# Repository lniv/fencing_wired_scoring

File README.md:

# A simple fencing scoring system

The aim is to make it simple, rather than efficient or super precise.\
Towards that, the hardware is a LED display with a matching controller from adafruit,
and circuitpython is used vs e.g. C. I tried to keep hardware to minimum, but pullup resisotrs appear necesssary for wired operation.

Note: foil only currently.

## Setup

### Display

#### Common to wired and wireless setups

These instructions assume a matrixportal-S3 is used as the display controller. There is nothing magical about it, but it is convenient.

- Install circuitpython on the matrixportal S3 : https://learn.adafruit.com/adafruit-matrixportal-s3/install-circuitpython
- Prep the portal and led display : https://learn.adafruit.com/adafruit-matrixportal-s3/prep-the-matrixportal
- Wire a buzzer between the A0 (battery connector) and ground.
- Copy [code.py](./code.py), [settings.toml](./settings.toml) and the various bmp files onto the circuitpython drive.

#### Additional display / connector setup for wired use:

I added the wireless option later, so e.g. the display legs or buzzer holder were integrated with parts that are necessary only for wired operation.

- Solder 2.2kohm (or similar) pullup resistors between the two weapon lines and 3V on the matriportalS3. These may not be necessary if you're using a different controller, in which case you should disable the pullup option ("HAVE_EXTERNAL_PULLUPS") in the settings.toml file.
- Print [display_connector.step](hardware/display_connector.step) and 2 or 3 of [display_leg](hardware/display_leg.step), and use a few M3x12 screws attach to display.
- Install and wire the six banana jacks.

### Wireless setups
- The two fencer boxes are described [here](./fencer_boxes/README.md).
- The display will create an AP with the ssid/password defined in the toml file - the default is ok for a single box.
- The three boxes can be powered on at any order, but if a fencer box doesn't find the AP, it will wait 5 sec before retrying, so if powered first you may have a 10 sec delay before hits can be registered.

## Usage
- Power display (and fencer boxes if used) via usb (typc-c, micro) connectors. The display likely needs ~ 10W.
- The display will setup up an AP (and operated in wireless mode) if the configuration file is deemed valid for wireless operation.
    - This can be overridden by holding the down button at startup.
- Audio can be enabled / disabled by holding the down button while a tip is pressed.
- Fence.

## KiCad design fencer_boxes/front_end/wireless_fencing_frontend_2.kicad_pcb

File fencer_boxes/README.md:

# Fencer boxes used for a wireless setup

Obviously you'd need two of these. Oveall, they're a combination of a picow (RP2040 based) or pico2w (RP2350 based) with a custom front end.

## Hardware setup
* make a front end (duh). The schematics and layout for the front end are in [here](./front_end).
    * The front end is not tightly tied to the pico(2) pinout, though the code is. The current design uses a TSSOP opamp, which is a bit challenging to solder manually, but the other components were kept to 0805 mostly. The setup is simple enough that it could be built on a generic TSSOP adapter, but at 1$/board throush oshpark, why bother.
    * Wiring for a pico-w/pico2-w:
        * 8 pin header:
            * 1 : Not connected
            * 2 : ground
            * 3 : 3.3V
            * 4 : GP9 (tip sense line)
            * 5 : Not connected
            * 6 : GP10 (tip pullup line)
            * 7 : GP13 (lame drive)
            * 8 : GP26/A0 (lame sense)
        * 3 pin header:
            * 1 : A (lame)
            * 2 : B (weapon / tip)
            * 3 : C (ground / common)
* I typically CA glue them to the pico and wire the connections.
* Have a mechanical setup with the three banana jacks, wired to the front end
* power is via the micro usb connector - I use a small usb battery pack.

## Software setup
* Install circuitpython onto the board; for a pico2w, [https://circuitpython.org/board/raspberry_pi_pico2_w/]
* copy [code.py](./code.py) onto the board
* copy the [settings.toml from the parent folder](../settings.toml) file onto the board AND modify it to select either "left" or "right" side.

## TODO:
* Add step files for suitable hardware boxes
* Add BOM
* Replace opamp with a soic part.

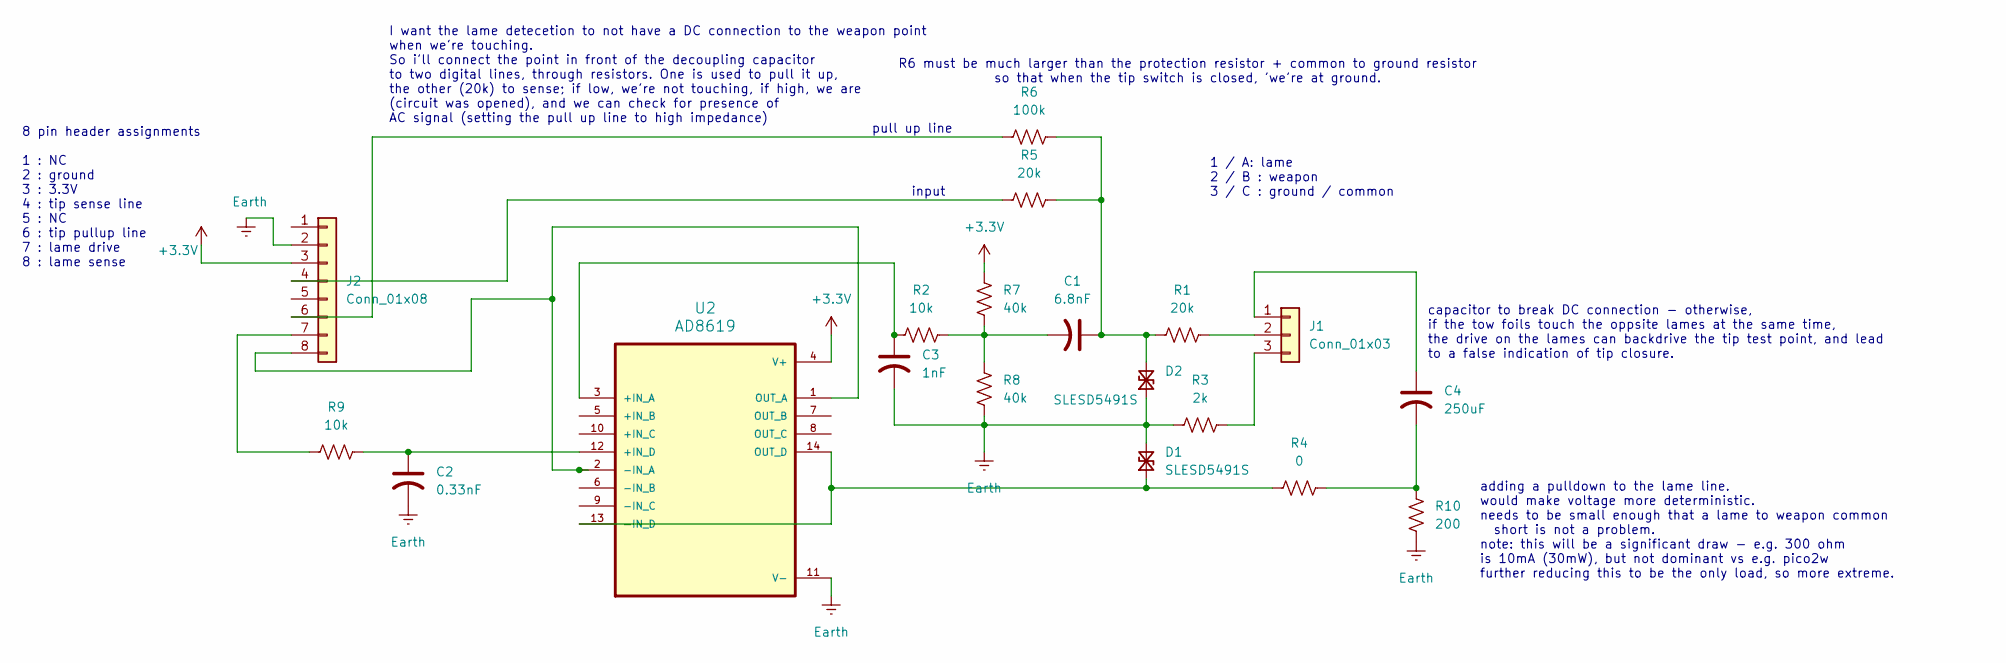
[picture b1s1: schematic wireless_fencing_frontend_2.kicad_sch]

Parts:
C1: 6.8nF; C_0805_2012Metric
C2: 0.33nF; C_0805_2012Metric
C3: 1nF; C_0805_2012Metric
C4: 250uF; C_0805_2012Metric
D1, D2: SLESD5491S; D_SOD-523
J1: Conn_01x03; PinHeader_1x03_P2.54mm_Vertical
J2: Conn_01x08; PinHeader_1x08_P2.54mm_Vertical
R1, R5: 20k; R_0805_2012Metric
R2, R9: 10k; R_0805_2012Metric
R3: 2k; R_0805_2012Metric
R4: 0; R_0805_2012Metric
R6: 100k; R_0805_2012Metric
R7, R8: 40k; R_0805_2012Metric
R10: 200; R_0805_2012Metric
U2: AD8619; SOP65P640X120-14N

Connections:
+3.3V: J2.3, R7.2, U2.4 (V+)
Earth: C2.2, C3.2, D1.2 (A2), D2.1 (A1), J2.2, R3.1, R8.1, R10.1, U2.11 (V-)
unnamed: C1.2, R2.1, R7.1, R8.2
unnamed: C4.2, R4.2, R10.2
unnamed: D1.1 (A1), R4.1, U2.13 (-IN_D), U2.14 (OUT_D)
unnamed: C1.1, D2.2 (A2), R1.1, R5.2, R6.1
unnamed: C4.1, J1.1
unnamed: J1.2, R1.2
unnamed: J1.3, R3.2
unnamed: J2.4, R5.1
unnamed: J2.6, R6.2
unnamed: J2.7, R9.1
unnamed: J2.8, U2.1 (OUT_A), U2.2 (-IN_A)
unnamed: C3.1, R2.2, U2.3 (+IN_A)
unnamed: C2.1, R9.2, U2.12 (+IN_D)

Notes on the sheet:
input
8 pin header assignments 1 : NC 2 : ground 3 : 3.3V 4 : tip sense line 5 : NC 6 : tip pullup line 7 : lame drive 8 : lame sense
R6 must be much larger than the protection resistor + common to ground resistor so that when the tip switch is closed, 'we're at ground.
pull up line
adding a pulldown to the lame line. would make voltage more deterministic. needs to be small enough that a lame to weapon common short is not a problem. note: this will be a significant draw - e.g. 300 ohm is 10mA (30mW), but not dominant vs e.g. pico2w further reducing this to be the only load, so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
capacitor to break DC connection - otherwise, if the tow foils touch the oppsite lames at the same time, the drive on the lames can backdrive the tip test point, and lead to a false indication of tip closure.
I want the lame detecetion to not have a DC connection to the weapon point when we're touching. So i'll connect the point in front of the decoupling capacitor to two digital lines, through resistors. One is used to pull it up, the other (20k) to sense; if low, we're not touching, if high, we are (c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
1 / A: lame 2 / B : weapon 3 / C : ground / common

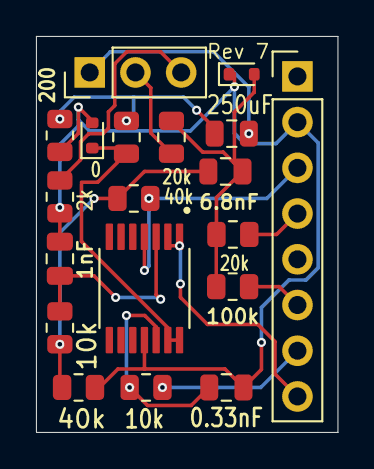
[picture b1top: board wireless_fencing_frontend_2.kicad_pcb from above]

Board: 2 copper layers, 16.8 x 22.0 mm, 19 parts (0 on the bottom side), 15 nets.

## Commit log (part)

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2025-11-12 initial draft - print tip / valid status
    i.e. not timing etc, and hw not quite there.
    mostly for timing checks - on a matrix portal S3 i get ~4msec worst case.
    barely acceptable.
2025-11-12 Adding hardware (3d printed parts) step files and mention in readme
2025-11-12 adding readme
2025-11-12 Adding image display on rgb matrix, test only
    i.e. have all images, and showing them, but commented out actually scoring.
    Note: need to copy the bmp file to the root of the drive togeter with code.py
2025-11-12 actual fencing loop.
    only announcing via console for now.
2025-11-12 Adding buzzer code (but no buzzer yet)
2025-11-12 blacking
2025-11-12 Adding hw description and 2.2kOhm pullups.
    set a global to control behavior, e.g. for testing new setups
    before soldering pullups.
    The pullups do seem to make everything more reliable, at least
    as tested so far on short (i.e. only body cord) lines.
2025-11-12 split early timing tests to separate file and cleanup a bit
2025-11-13 move adding tiles to end of action
    added some debug "telemetry" for worst cycle since last action -
    This showed ~20 msec, which convinced me that we should try to improve it.
    Not surprisingly, adding the image to the tile was slow, so moving it helped.
    Also structured the loop so we don't check a side that's been announced (i.e.
    detected a touch) in the remaining time till lockout expires.
    I now see ~5 msec worst case, more typical 2 - 3 msec for the worst cycle.
2025-11-16 buzzer code cleanup and adjusting freq to hw used.
2025-11-16 Adding step file for simple buzzer holder for a PS1240P02BT
    or anything else at 12.2mm diameter.
    attach over the banana jack holder that mounts to the display,
    using a longer M3 screw (16mm vs 12 mm)
    could merge it onto the banana plug holder, but chose to keep
    separate (and added later...)
2025-11-17 fix reference and minimal contact time (for foil)
    note : since our cycle time is a few msec (typical ~ 2msec, worst case ~5msec),
    we don't actually conform to the +-1 msec contact time requirements.
2025-11-23 fixed actually using lockout timing...
    at some point when i modified code it went unused.
    linting etc would have helped in this case.
2025-12-25 Adding R and G to the red and green hit indicators
2025-12-30 Change timing of showing results to fencer
    1. buzzer start immediately on first hit detected (instead of after action
    ends)
    2. optional (defaults false, since it's slow atm), update display when the
    hit is detected, rather than waiting for the end of the action. This takes
    20 msec roughly, which is too slow imo during action.
    3. buzz an additional time after action is ended (i.e. up to lockout time +
2025-12-30 removing frame wait when adding image to display stack
    left he instrumentation / prints that showed that it was the major
    time consumer.
    left the default of not displaying images immediately, even though
    these take ~ 3 - 4 msec extra (conpared to 0.15msec without) and this
    is probably ok, since i think i can improve things further.
2025-12-30 preloading bitmaps in an attempt to save time
    that didn't work - it is faster (by ~ 1 msec) most of the time,
    BUT, it occasionally blows to ~ 15 msec! tried garbage collecting,
    but this did nothing useful.
2026-01-11 Adding wireless option
    dependent on setting.toml file, and (duh) fencer side boxes.
    those are still in a separate repo, and need to be combined.
2026-01-13 Moving remainder settings from python to settings.toml
2026-01-18 Adding description of wireless fencer boxes
    i.e. schematics and layout, code
    * i haven't yet marged the settings.toml file
    This was originally developed in a separate repo; i decided to lose the
    history and copied the files over.
2026-01-19 Combined settings.toml file and settled on time units
    also
    * can recover from the display being reset, recreating the connection to the AP
    * maybe fixed a small bug in checking the tip status (with the RP2350
    E9 bug)
    Not quite sure the acceptance of messages beyond the strict lockout (with lockout
    timing check used to validate them) is working correctly; I think i see a bogus hit on a next
2026-01-19 Fix looking for late messages beyond lockout time
2026-01-19 drain socket before beginning next action
    solves the phantom hits coming in later
2026-01-19 When starting, will retry till connecting to AP
    rather than just fail and require reboot.
    this allows the display to be brought up after the fencer boxes
2026-01-20 fix lame drive component values
    not sure these are final (higher f0 than i think is warranted),
    but seem to work ok and what i had was bad (i.e. different than
    intended and not working...)
2026-01-20 adjust valid power threshold
    working value for now; we'll see if it's too marginal, or if a
    different approach is needed for measuring the AC power.
2026-01-20 Adding front end to pico wiring assignments in readme
2026-01-20 front end tvs and resistor combination
    * Single SOD-523 footprint for TVS diodes
    * Changed from using 2x20kOhm in series to single 40kOhm.
    Initially was trying to minimize the number of different values, but resistors
    are like a cent a piece, even in pretty small quantities, and this saves soldering.
2026-01-24 checking touch validity should finish before min touch time
    timed the processing time, adjusted settings so that we can sample for a sane time,
    then process, and have some some spare time (which we spend in a busy loop) till
    the debounce window finishes.
2026-01-24 Shorten sleep times - can hit immediately, and display shorter time
    the previous times proved annoying when testing it.
2026-01-26 image addition in real time controlled via settings.toml
    defaults to true, which is less of an issue for a wireless setup,
    partially cause i also am now dumping packets that arrived while
    processing a hit, so that i don't mark a it as 20 msec late.
    (hard to test manually if all this works ok, however)
2026-01-26 fix bug where we accepeted new hit after announcing a side.
    this in effect reopened the lockout time, which is obviously wrong.
2026-01-27 for wireless setups, inhibit buzzer if right A and shorted.
    checks each time we reset status, applies to next action.
    a bit of a kludge, but i have the jacks wired...
2026-01-27 shortening message repeat delays and overall max send period
2026-01-31 setting min valid touch back to 8e10
    when you're shorting the two sides with your hand, there are less issues :)
2026-02-07 Allow forcing wired mode by holding the down button during startup.
2026-02-07 show different logo at start for wired vs wireless modes
2026-02-07 silent / noisy controlled by same button used to select modes
    i.e. no longer by shorting A-C in wireless mode and nothing in wired.
2026-02-07 fix audio status to be toggled by button press, not set.
    previous logic made sense when i was using a shorting wire.
    Also made the default controlled by the settings file.
    (with the note that it will get flipped at start if you're using
    the button to override wireless mode)
2026-02-08 reverting to a lower threshold for a valid hit
    the higher one ended up being too high when i wasn't actually touching
    the lame - apparently that changed the coupling more than i thought.
2026-02-13 Adjusting parameters - together with a low pass filter added, work ok
    or barely acceptable, but maybe the best that can be done for now.
    I added a 11kohm / 1nF passive low pass - i forgot to put an anti alias
    in the design. Bumped up sampling to 80kHz, and shortened collection time
    (cause 5 msec for a 7/8kHz signal is plenty enough, i think)
2026-02-22 major data processing changes
    * tip pullup is kept high other then when getting ac data
    * when waiting for hit, minimal busy loop just checking tip status
    * float tip, wait, collect AC data
    * reset tip status, then wait for minimal time to pass (if needed)
    * if hit is valid, then process data (i.e. outside of critical time)
    * data processing now has
2026-02-22 going to higher frequencies - 11, 13 kHz
    i seem to get a bit better SNR here, and it's within same filters.
    may want to investigate going much higher (but keeping in mind an 83kHz
    adc limit if i want to use an esp32-s3 in the future)
2026-03-02 moving validity call to display
    * calculating power at a target and base freuqency, sending values
    to display. Processign is about 25 msec on the p2350, but it's the
    same on both sides, so not an issue there, and still much faster than
    human times.
    * call on validity made there, currently absolute + ratio limits
    * timed at 0.2-0.3msec, so accetable.
2026-03-05 switch to using spectrogram rather than the Goertzel filters
    seems to work better in stationary testing, but i'm not sure how much
    margin i really have - i might need hardware changes to get stronger signal.
    Analysis may actually be faster - takes 1.4 or 3.4 msec (seems bistable)
    this uses a ulab pre compiled function...
    * since the ulab spectrogram (welch) requires power of 2 samples,
    adjust sampling time to match that.
2026-03-05 remove commented out code
    * remains of debugging
    * the Goertzel algorithm and calls
    * the median filter
2026-03-06 redo validity criteria - off peak calc and use
    * rather than fixed base (non peak) frequency, specify a delta offset
    and use the mean value of the psd at this (approximate) offset above and
    below the peak frequency.
    * validity criteria changed so that the min peak/off peak ratio is multiplied
    by the (relative to the threshold) strength of the signal, so that a very prominent
    signal can be marginal and vice versa.
2026-03-07 Adding simple passive lowpass before adc buffer
    set to 10k, 1nF i.e. f0 16kHz ; used 11k, not critical.
    i've bodged this into the existing boards.
2026-03-09 change off peak index calculation to ensure symmetry
2026-03-15 lame drive changed from 20k to 2k
    just matching change in reality; not sure if it's important.
2026-03-29 Adding lame pulldown and common line to ground resistor
    so now the lame connection is
    1. on a voltage divider between the drive and ground, not floating.
    2. setting this to 100 ohm drive, 200 ohm to ground - so also much stronger than before.
    and the C (common) line is not tied directly to ground, but has a 2k resistor.
    Overall, this doesn't change the tip detection much, but should make the lame drive more
    resistant to the common line touching the lame (cause of e.g. sweaty skin). Before this
2026-03-30 Change to AC coupling of drive to lame
    i.e. add a capacitor on the line.
    with the recent addition of tying the lame drive to ground, if one
    foil touches the opposite lame, the moment the other touch happens -
    - even before the switch is actually depressed - the voltage at the
    pin can be back driven by the (opposite) lame and trigger a false touch.
    Braking the DC coupling solves it.
2026-04-13 Adjusting lame drive hardware for a stronger drive
    * reduce (well, eliminate) the inline resistance (i think not needed
    once we're capacitively coupled to the lame)
    * increase the capacitor from 100nF to 10uF.
    Both of these changes seem to do better when the lame is "shorted" to
    the common line; the current configs seem to do ok down to about 5kOhm
    of a short, but no lower - so a super sweaty fencer is still an issue,
2026-04-20 two way comm - display acknowledges messages from boxes
    For the display it's a very minimal change - it replies to the sending
    address with a copy of what it received.
    On the fencer box side,
    * Once we receive a reply, we stop sending repeats.
    better behavior when two are sending in close proximity (before i
    relied on the random delays + repeeats, but i think it wasn't
2026-04-23 NOT dumping packets during an action
    since we now will stop sending once we got an acknowledgment,
    it's better if we have a stale (relatively) packet rather than
    force a resend; the time limits i have a short enough that we might
    not get the resend through - which i think i've seen happen.
    note that we might want to set configs so we only send once,
    or drop adding the sending time to the allowed lockout time.
2026-05-01 Switch to TCP communication
    Seems to do better on normal use (i.e. actually timely manner of receiving
    hits), BUT, doesn't recover nicely if the display reboots (or likely if
    we drop the connection for other reasons)
    needs cleanup and refactoring.
2026-05-01 refactor the core to a class
    mostly to have the socket as a class attribute, not a global.
    note that the overall constants setup, and some hardware methods
    are outside the class.
2026-05-01 change lame capacitor to 250 uF
    seems to handle sweat etc better
